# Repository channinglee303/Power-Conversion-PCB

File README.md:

# Power Conversion PCB

This repository contains the KiCad design files for the Lightning from the Edge of Space research project power board made fall 2026. The board is designed to accept power from a 6S LiPo battery, provide input protection, and generate adjustable DC output for other LEOS components. This board also includes the standard Raspberry Pi Pico and CAN-FD network.

The design uses a Texas Instruments TPS16630 eFuse for input protection and two TPS54540B buck converters for voltage regulation. A Raspberry Pi Pico controls the output voltage through the MCP41100 SPI digital potentiometer in one of the buck converter's feedback network. 

The target output ranges are 5V at up to 5A and 1-18V at up to 5A. 

# Board Overview
The power board has three main functions:
Input protection: A TPS16630 eFuse provides adjustable undervoltage lockout, overvoltage protection, current limiting, and controlled startup.
DC-DC conversion: Two TPS54540B switching buck converters step down the battery voltage to both a fixed and adjustable output voltage.
Digital control: A Raspberry Pi Pico communicates with an MCP41100 digital potentiometer over SPI to adjust one of the buck converters' feedback resistance.

# Electrical design targets
Input source: 6S LiPo battery
Nominal input voltage: 22.2V
Fully charged battery voltage: 25.2V
Input undervoltage cutoff: Approximately 19-19.5V
Output voltage: 5V and approximately 1-18V adjustable 
Maximum output current: 5A
Buck converter: TPS54540B
eFuse: TPS16630
Digital potentiometer: MCP41100T-I/SN
Control interface: SPI from Raspberry Pi Pico
CAN-FD controller: MCP2518FD
CAN-FD transceiver: MCP2562FD

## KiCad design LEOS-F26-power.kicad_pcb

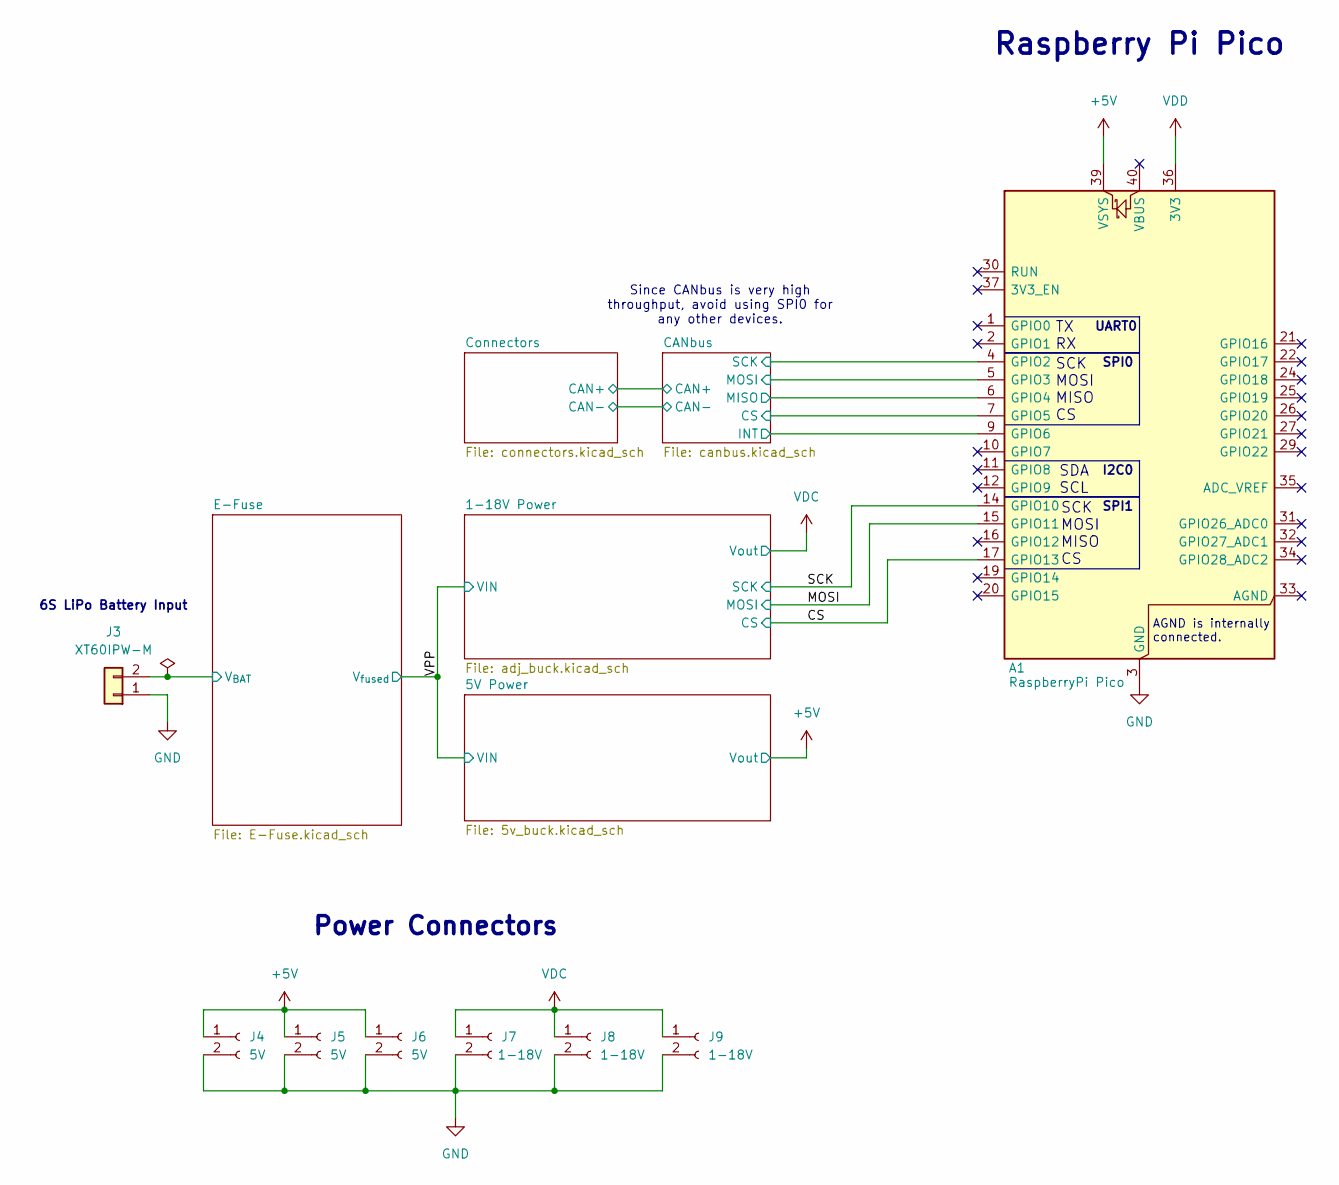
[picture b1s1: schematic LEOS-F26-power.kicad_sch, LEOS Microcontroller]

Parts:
A1: RaspberryPi Pico; RaspberryPi_Pico_Common_Unspecified; MPN PIM724; Digikey 1778-PIM724-ND
J3: XT60IPW-M; AMASS_XT60IPW-M_1x03_P7.20mm_Horizontal
J4, J5, J6: 5V; JST_XH_S2B-XH-A_1x02_P2.50mm_Horizontal; MPN S2B-XH-A; Digikey 455-S2B-XH-A-ND
J7, J8, J9: 1-18V; JST_XH_S2B-XH-A_1x02_P2.50mm_Horizontal; MPN S2B-XH-A; Digikey 455-S2B-XH-A-ND

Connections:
+5V: A1.39 (VSYS), J4.1, J5.1, J6.1; also elsewhere on the board
/CANbus/CS: A1.7 (GPIO5); also elsewhere on the board
/CANbus/INT: A1.9 (GPIO6); also elsewhere on the board
/CANbus/MISO: A1.6 (GPIO4); also elsewhere on the board
/CANbus/MOSI: A1.5 (GPIO3); also elsewhere on the board
/CANbus/SCK: A1.4 (GPIO2); also elsewhere on the board
/CS: A1.17 (GPIO13); also elsewhere on the board
/E-Fuse/V_{BAT}: J3.2; also elsewhere on the board
/MOSI: A1.15 (GPIO11); also elsewhere on the board
/SCK: A1.14 (GPIO10); also elsewhere on the board
GND: A1.3 (GND), A1.8 (GND), A1.13 (GND), A1.18 (GND), A1.23 (GND), A1.28 (GND), A1.38 (GND), J3.1, J4.2, J5.2, J6.2, J7.2, J8.2, J9.2; also elsewhere on the board
VDC: J7.1, J8.1, J9.1; also elsewhere on the board
VDD: A1.36 (3V3); also elsewhere on the board

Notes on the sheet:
SPI1
Raspberry Pi Pico
SCK MOSI MISO CS
Power Connectors
Since CANbus is very high throughput, avoid using SPI0 for any other devices.
SPI0
SDA SCL
TX RX
6S LiPo Battery Input
UART0
I2C0
AGND is internally connected.

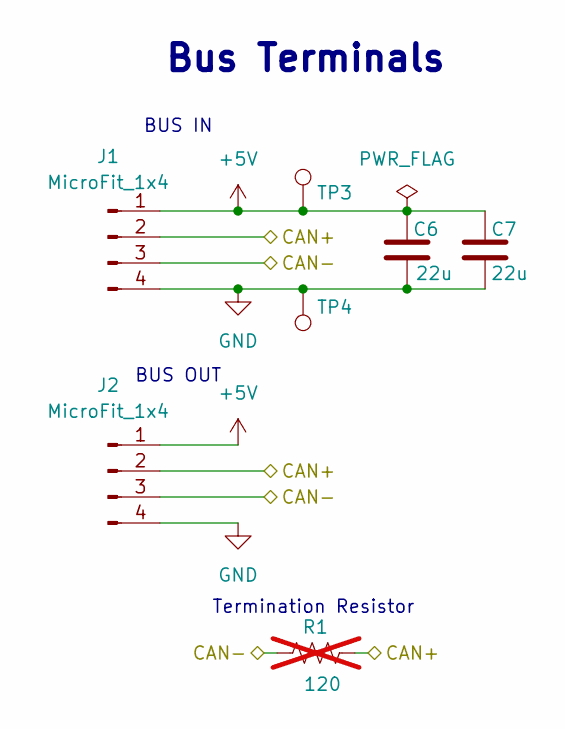
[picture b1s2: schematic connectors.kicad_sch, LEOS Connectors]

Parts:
C6, C7: 22u; C_1206_3216Metric; MPN CL31A226MOCLNNC; Digikey 1276-2728-1-ND
J1, J2: MicroFit_1x4; Molex_MicroFit3.0_43650-0410_1x04_Horizontal; MPN 0436500409; Digikey WM1882CT-ND
R1: 120; R_Axial_DIN0207_L6.3mm_D2.5mm_P7.62mm_Horizontal; MPN CF14JT120R; Digikey CF14JT120RCT-ND; not fitted
TP3: 5V Test Point; TestPoint_Loop_D2.60mm_Drill0.9mm_Beaded; MPN 5000; Digikey 36-5000-ND
TP4: GND Test Point; TestPoint_Loop_D2.60mm_Drill0.9mm_Beaded; MPN 5001; Digikey 36-5001-ND

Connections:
+5V: C6.1, C7.1, J1.1, J2.1, TP3.1 (1_1); also elsewhere on the board
/CANbus/CAN+: J1.2, J2.2, R1.2; also elsewhere on the board
/CANbus/CAN-: J1.3, J2.3, R1.1; also elsewhere on the board
GND: C6.2, C7.2, J1.4, J2.4, TP4.1 (1_1); also elsewhere on the board

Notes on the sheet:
BUS OUT
Bus Terminals
BUS IN
Termination Resistor

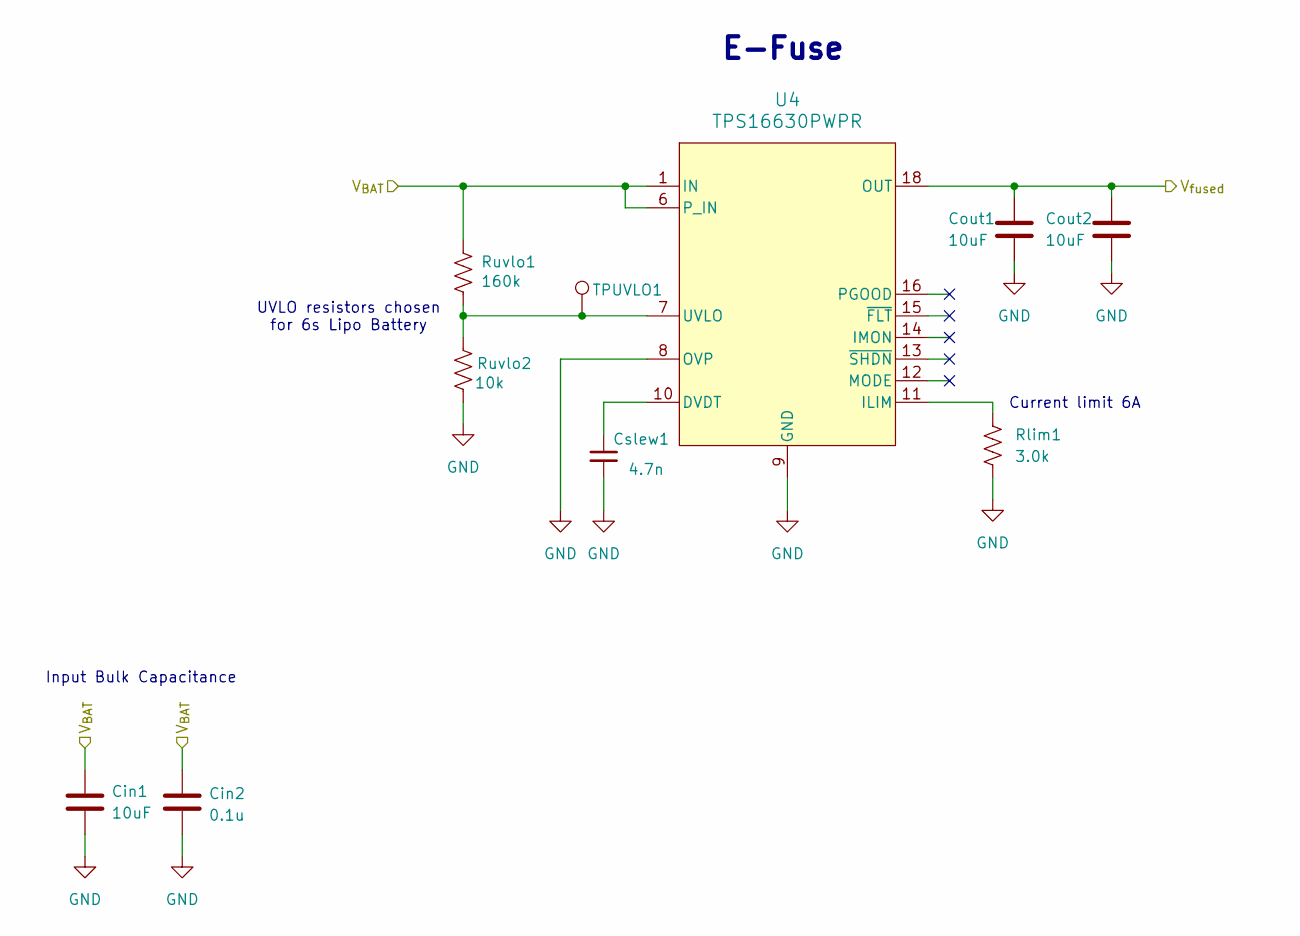
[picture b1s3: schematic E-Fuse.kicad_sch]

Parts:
Cin1: 10uF; C_0805_2012Metric; MPN GRM21BR61E106MA73L; Digikey 490-10748-1-ND
Cin2: 0.1u; C_0805_2012Metric; MPN CL21B104KBCNNNC; Digikey 1276-1003-1-ND
Cout1, Cout2: 10uF; C_0805_2012Metric; MPN GRM21BR61E106MA73L; Digikey 490-10748-1-ND
Cslew1: 4.7n; C_0805_2012Metric; MPN C0805C472J3GEC7210; Digikey 399-C0805C472J3GEC7210CT-ND
Rlim1: 3.0k; R_0805_2012Metric; MPN RMCF0805FT3K00; Digikey RMCF0805FT3K00CT-ND
Ruvlo1: 160k; R_Axial_DIN0207_L6.3mm_D2.5mm_P10.16mm_Horizontal; MPN MFR-25FTE52-160K; Digikey 13-MFR-25FTE52-160KCT-ND
Ruvlo2: 10k; R_Axial_DIN0207_L6.3mm_D2.5mm_P10.16mm_Horizontal; MPN MFR-25FRF52-10K; Digikey 13-MFR-25FRF52-10KCT-ND
TPUVLO1: TestPoint; TestPoint_Loop_D2.60mm_Drill0.9mm_Beaded
U4: TPS16630PWPR; HTSSOP20_PWP_TEX; MPN TPS16630PWPT; Digikey 296-TPS16630PWPTCT-ND

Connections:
/E-Fuse/V_{BAT}: Cin1.1, Cin2.1, Ruvlo1.1, U4.1 (IN), U4.2 (IN), U4.3 (IN), U4.6 (P_IN); also elsewhere on the board
/VPP: Cout1.1, Cout2.1, U4.18 (OUT), U4.19 (OUT), U4.20 (OUT); also elsewhere on the board
GND: Cin1.2, Cin2.2, Cout1.2, Cout2.2, Cslew1.2, Rlim1.2, Ruvlo2.2, U4.8 (OVP), U4.9 (GND), U4.21 (GND); also elsewhere on the board
unnamed: Cslew1.1, U4.10 (DVDT)
unnamed: Rlim1.1, U4.11 (ILIM)
unnamed: Ruvlo1.2, Ruvlo2.1, TPUVLO1.1 (1_1), U4.7 (UVLO)

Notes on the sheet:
UVLO resistors chosen for 6s Lipo Battery
Current limit 6A
Input Bulk Capacitance
E-Fuse

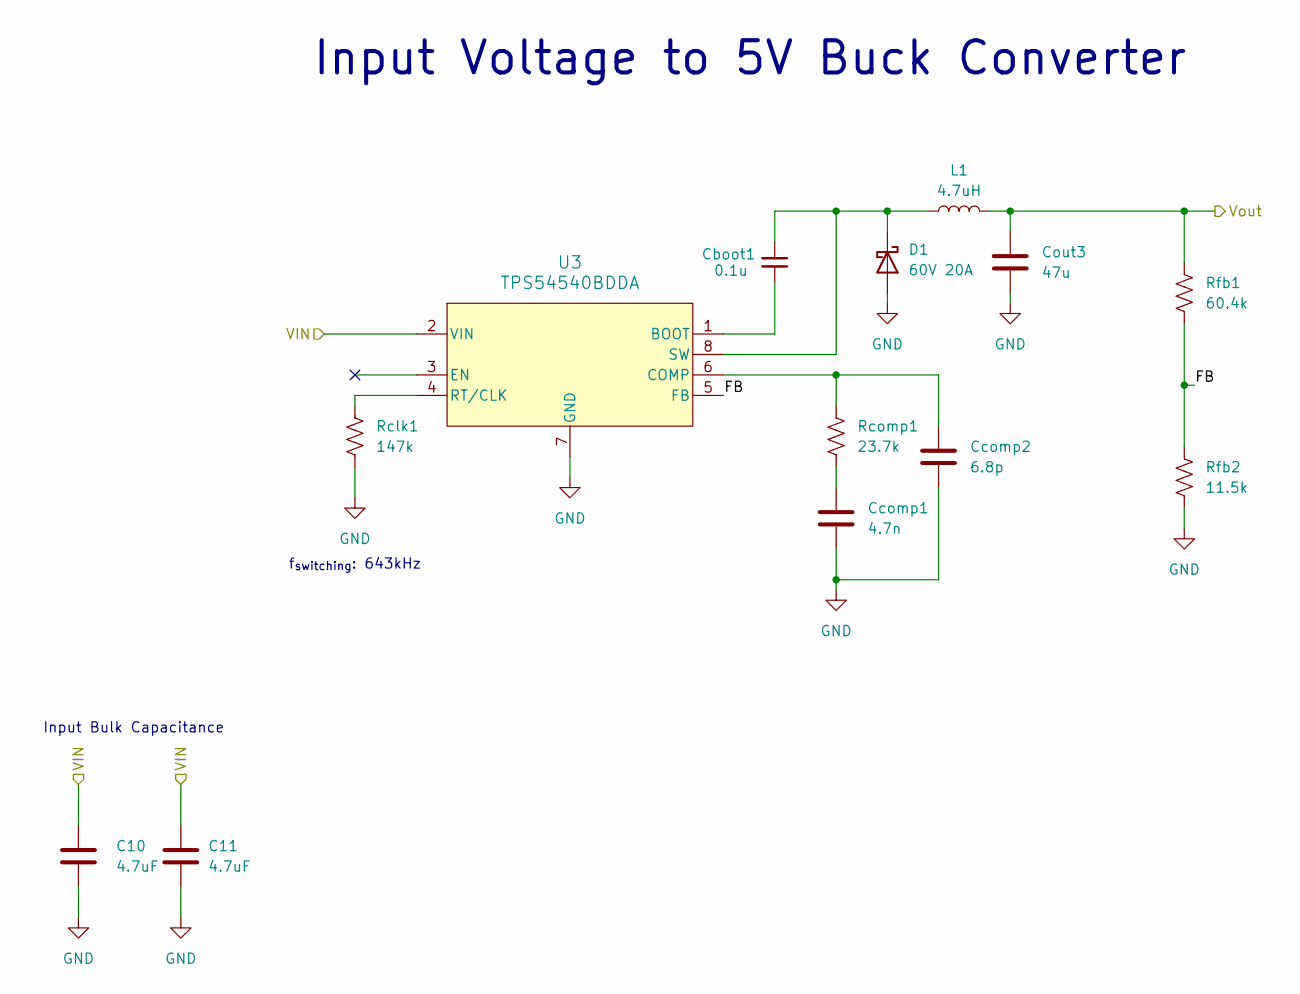
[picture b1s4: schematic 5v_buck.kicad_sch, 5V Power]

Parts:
C10, C11: 4.7uF; C_0805_2012Metric; MPN CL21A475KBQNNNE; Digikey 1276-1248-1-ND
Cboot1: 0.1u; C_0805_2012Metric; MPN CL21B104KBCNNNC; Digikey 1276-1003-1-ND
Ccomp1: 4.7n; C_0805_2012Metric; MPN C0805C472J3GEC7210; Digikey 399-C0805C472J3GEC7210CT-ND
Ccomp2: 6.8p; C_0805_2012Metric; MPN C0805C689C3HACAUTO; Digikey 399-C0805C689C3HACAUTOCT-ND
Cout3: 47u; CAPAE660X600N; MPN A768EB476M1VLAE042; Digikey 399-A768EB476M1VLAE042CT-ND
D1: 60V 20A; D_DO-201AD_P15.24mm_Horizontal; MPN SB2060; Digikey 1655-SB2060CT-ND
L1: 4.7uH; IND_SRP7028A-4R7M_BRN; MPN SRP7028A-4R7M; Digikey SRP7028A-4R7MCT-ND
Rclk1: 147k; R_0805_2012Metric; MPN RMCF0805FT147K; Digikey RMCF0805FT147KCT-ND
Rcomp1: 23.7k; R_0805_2012Metric; MPN RMCF0805FT23K7; Digikey 738-RMCF0805FT23K7CT-ND
Rfb1: 60.4k; R_0805_2012Metric; MPN RMCF0805FT60K4; Digikey RMCF0805FT60K4CT-ND
Rfb2: 11.5k; R_0805_2012Metric; MPN RMCF0805FT11K5; Digikey RMCF0805FT11K5CT-ND
U3: TPS54540BDDA; SO-POWERPAD8_DDA_TEX; MPN TPS54540BDDA; Digikey 296-TPS54540BDDA-ND

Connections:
+5V: Cout3.1, L1.2, Rfb1.1; also elsewhere on the board
/5V Power/FB: Rfb1.2, Rfb2.1, U3.5 (FB)
/VPP: C10.1, C11.1, U3.2 (VIN); also elsewhere on the board
GND: C10.2, C11.2, Ccomp1.2, Ccomp2.2, Cout3.2, D1.2 (A), Rclk1.2, Rfb2.2, U3.7 (GND), U3.EPAD (GND); also elsewhere on the board
unnamed: Ccomp1.1, Rcomp1.2
unnamed: Cboot1.2, D1.1 (K), L1.1, U3.8 (SW)
unnamed: Cboot1.1, U3.1 (BOOT)
unnamed: Ccomp2.1, Rcomp1.1, U3.6 (COMP)
unnamed: Rclk1.1, U3.4 (RT/CLK)

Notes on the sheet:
Input Bulk Capacitance
f_{switching}: 643kHz
Input Voltage to 5V Buck Converter

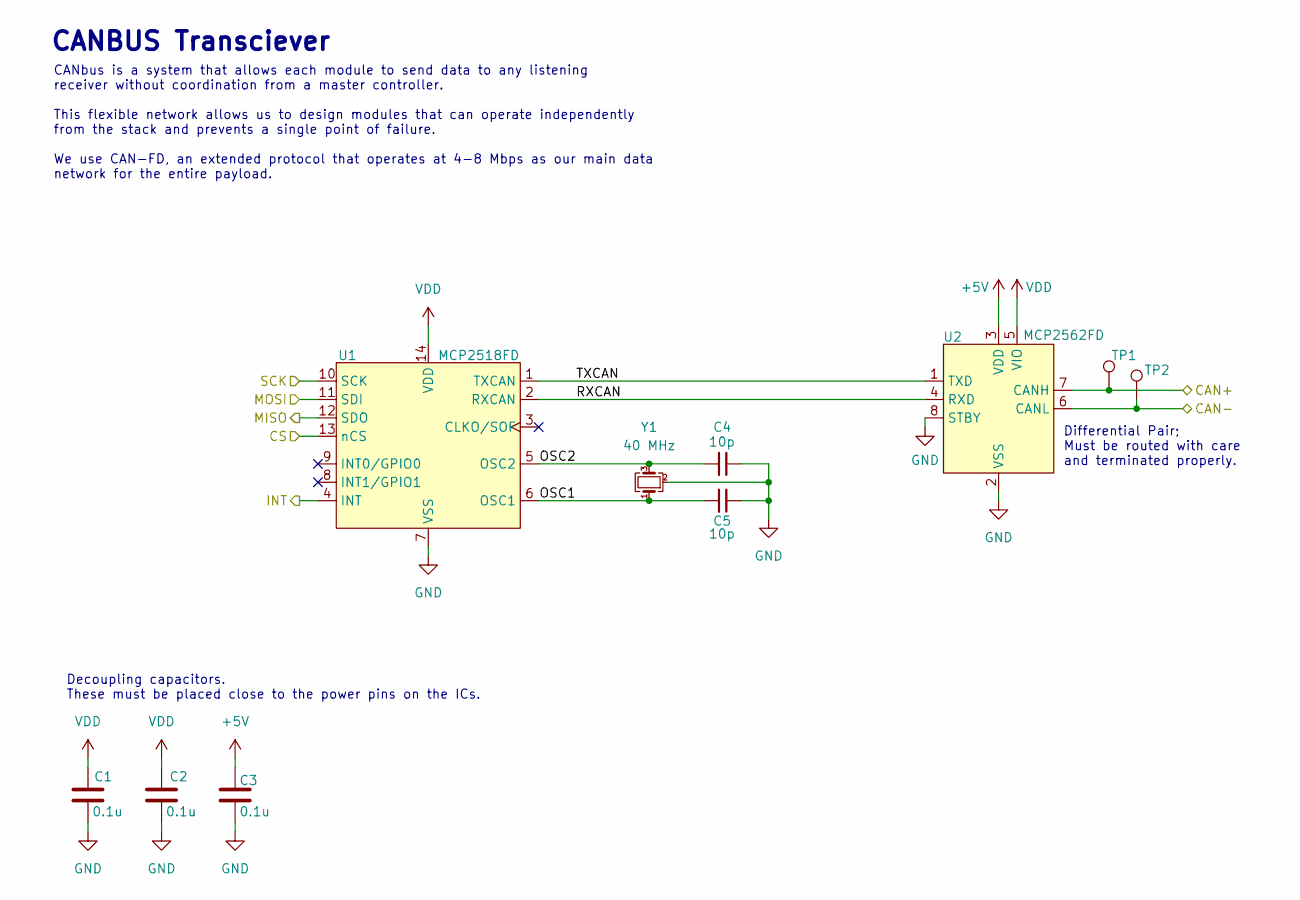
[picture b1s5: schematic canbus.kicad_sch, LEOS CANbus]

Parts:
C1, C2, C3: 0.1u; C_0805_2012Metric; MPN CL21B104KBCNNNC; Digikey 1276-1003-1-ND
C4, C5: 10p; C_0805_2012Metric; MPN CL21C100CBANNNC; Digikey 1276-2561-1-ND
TP1: CAN-H Test Point; TestPoint_Loop_D2.60mm_Drill0.9mm_Beaded; MPN 5004; Digikey 36-5004-ND
TP2: CAN-L Test Point; TestPoint_Loop_D2.60mm_Drill0.9mm_Beaded; MPN 5116; Digikey 36-5116-ND
U1: MCP2518FD; SOIC-14_3.9x8.7mm_P1.27mm; MPN MCP2518FDT-E/SL; LCSC C626758
U2: MCP2562FD; SOIC-8_3.9x4.9mm_P1.27mm; MPN MCP2562FDT-H/SN; LCSC C511335
Y1: 40 MHz; Crystal_SMD_2016-4Pin_2.0x1.6mm; MPN ECS-400-10-37B2-CKY-TR; Digikey 50-ECS-400-10-37B2-CKY-TRCT-ND

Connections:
+5V: C3.1, U2.3 (VDD); also elsewhere on the board
/CANbus/CAN+: TP1.1 (1_1), U2.7 (CANH); also elsewhere on the board
/CANbus/CAN-: TP2.1 (1_1), U2.6 (CANL); also elsewhere on the board
/CANbus/CS: U1.13 (nCS); also elsewhere on the board
/CANbus/INT: U1.4 (INT); also elsewhere on the board
/CANbus/MISO: U1.12 (SDO); also elsewhere on the board
/CANbus/MOSI: U1.11 (SDI); also elsewhere on the board
/CANbus/OSC1: C5.2, U1.6 (OSC1), Y1.1
/CANbus/OSC2: C4.2, U1.5 (OSC2), Y1.3
/CANbus/RXCAN: U1.2 (RXCAN), U2.4 (RXD)
/CANbus/SCK: U1.10 (SCK); also elsewhere on the board
/CANbus/TXCAN: U1.1 (TXCAN), U2.1 (TXD)
GND: C1.2, C2.2, C3.2, C4.1, C5.1, U1.7 (VSS), U2.2 (VSS), U2.8 (STBY), Y1.2 (G), Y1.4 (G); also elsewhere on the board
VDD: C1.1, C2.1, U1.14 (VDD), U2.5 (VIO); also elsewhere on the board

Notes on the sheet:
Differential Pair; Must be routed with care and terminated properly.
CANBUS Transciever
CANbus is a system that allows each module to send data to any listening receiver without coordination from a master controller. This flexible network allows us to design modules that can operate independently from the stack and prevents a single point of failure. We use CAN-FD, an extended protoco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
Decoupling capacitors. These must be placed close to the power pins on the ICs.

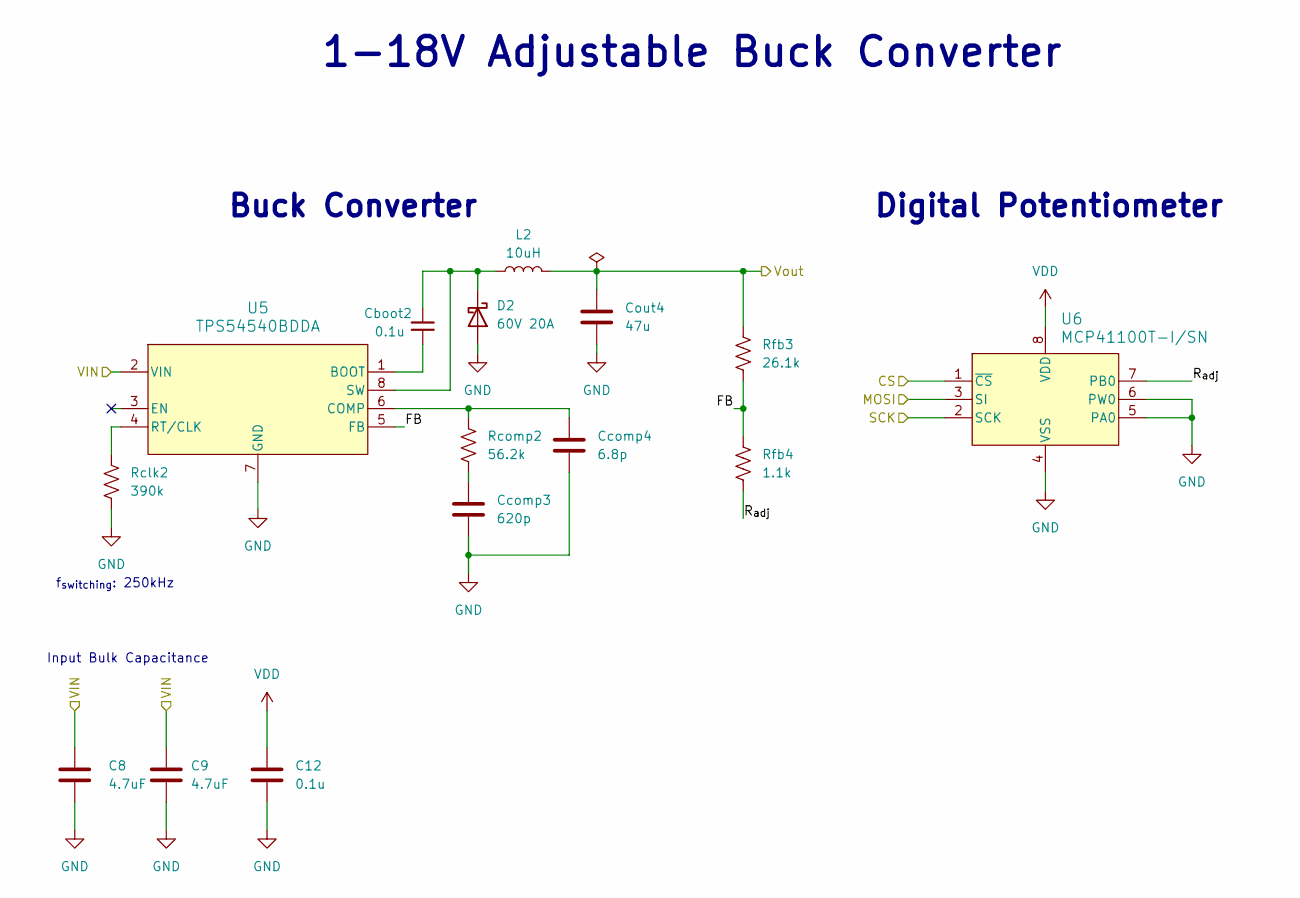
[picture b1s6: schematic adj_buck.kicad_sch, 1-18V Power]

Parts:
C8, C9: 4.7uF; C_0805_2012Metric; MPN CL21A475KBQNNNE; Digikey 1276-1248-1-ND
C12: 0.1u; C_0805_2012Metric; MPN CL21B104KBCNNNC; Digikey 1276-1003-1-ND
Cboot2: 0.1u; C_0805_2012Metric; MPN CL21B104KBCNNNC; Digikey 1276-1003-1-ND
Ccomp3: 620p; C_0805_2012Metric; MPN GRM2165C1H621JA01D; Digikey 490-1618-1-ND
Ccomp4: 6.8p; C_0805_2012Metric; MPN C0805C689C3HACAUTO; Digikey 399-C0805C689C3HACAUTOCT-ND
Cout4: 47u; CAPAE660X600N; MPN A768EB476M1VLAE042; Digikey 399-A768EB476M1VLAE042CT-ND
D2: 60V 20A; D_DO-201AD_P15.24mm_Horizontal; MPN SB2060; Digikey 1655-SB2060CT-ND
L2: 10uH; IND_BOURNS_SRR1280; MPN SRR1280-100M; Digikey SRR1280-100MCT-ND
Rclk2: 390k; R_0805_2012Metric; MPN RMCF0805FT390K; Digikey RMCF0805FT390KCT-ND
Rcomp2: 56.2k; R_0805_2012Metric; MPN RMCF0805FT56K2; Digikey RMCF0805FT56K2CT-ND
Rfb3: 26.1k; R_0805_2012Metric; MPN RMCF0805FT26K1; Digikey RMCF0805FT26K1CT-ND
Rfb4: 1.1k; R_0805_2012Metric; MPN RMCF0805FT1K10; Digikey RMCF0805FT1K10CT-ND
U5: TPS54540BDDA; SO-POWERPAD8_DDA_TEX; MPN TPS54540BDDA; Digikey 296-TPS54540BDDA-ND
U6: MCP41100T-I/SN; SOIC-8_3.9x4.9mm_P1.27mm; MPN MCP41100T-I/SN; Digikey MCP41100T-I/SNCT-ND

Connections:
/1-18V Power/FB: Rfb3.2, Rfb4.1, U5.5 (FB)
/1-18V Power/R_{adj}: Rfb4.2, U6.7 (PB0)
/CS: U6.1 (~CS); also elsewhere on the board
/MOSI: U6.3 (SI); also elsewhere on the board
/SCK: U6.2 (SCK); also elsewhere on the board
/VPP: C8.1, C9.1, U5.2 (VIN); also elsewhere on the board
GND: C8.2, C9.2, C12.2, Ccomp3.2, Ccomp4.2, Cout4.2, D2.2 (A), Rclk2.2, U5.7 (GND), U5.EPAD (GND), U6.4 (VSS), U6.5 (PA0), U6.6 (PW0); also elsewhere on the board
unnamed: Ccomp3.1, Rcomp2.2
unnamed: Cboot2.1, D2.1 (K), L2.1, U5.8 (SW)
unnamed: Cboot2.2, U5.1 (BOOT)
unnamed: Ccomp4.1, Rcomp2.1, U5.6 (COMP)
unnamed: Rclk2.1, U5.4 (RT/CLK)
VDC: Cout4.1, L2.2, Rfb3.1; also elsewhere on the board
VDD: C12.1, U6.8 (VDD); also elsewhere on the board

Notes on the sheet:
1-18V Adjustable Buck Converter
Digital Potentiometer
f_{switching}: 250kHz
Buck Converter
Input Bulk Capacitance

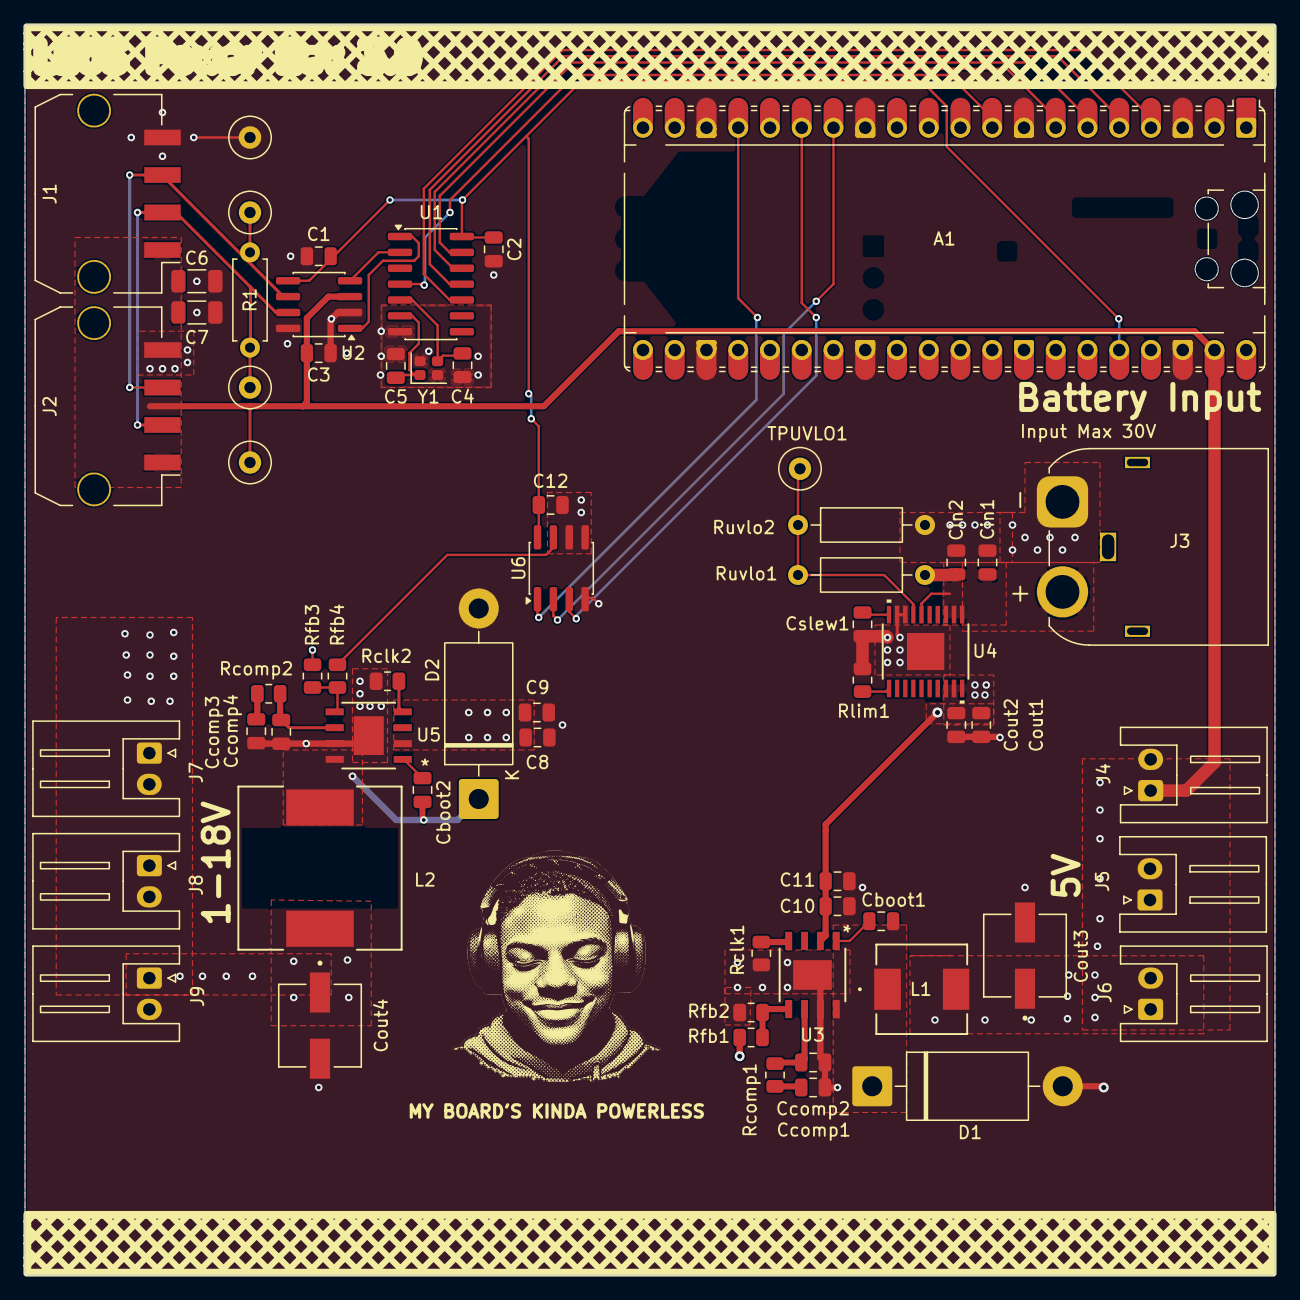
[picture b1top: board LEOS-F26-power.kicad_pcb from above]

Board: 4 copper layers, 100.0 x 100.0 mm, 63 parts (0 on the bottom side), 36 nets.
